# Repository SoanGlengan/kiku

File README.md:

# kiku
<h2>meshtastic device but open source</h2>
<p>small meshtastic device that is using a esp32 and sx1262</p>

<a href="https://docs.google.com/spreadsheets/d/1daOj9rbJtqAOdZNNDehtXnfdnzQVLjkryvcnbeCaL2A/edit?usp=sharing"><b>The Bill of Materials<b/><a/>

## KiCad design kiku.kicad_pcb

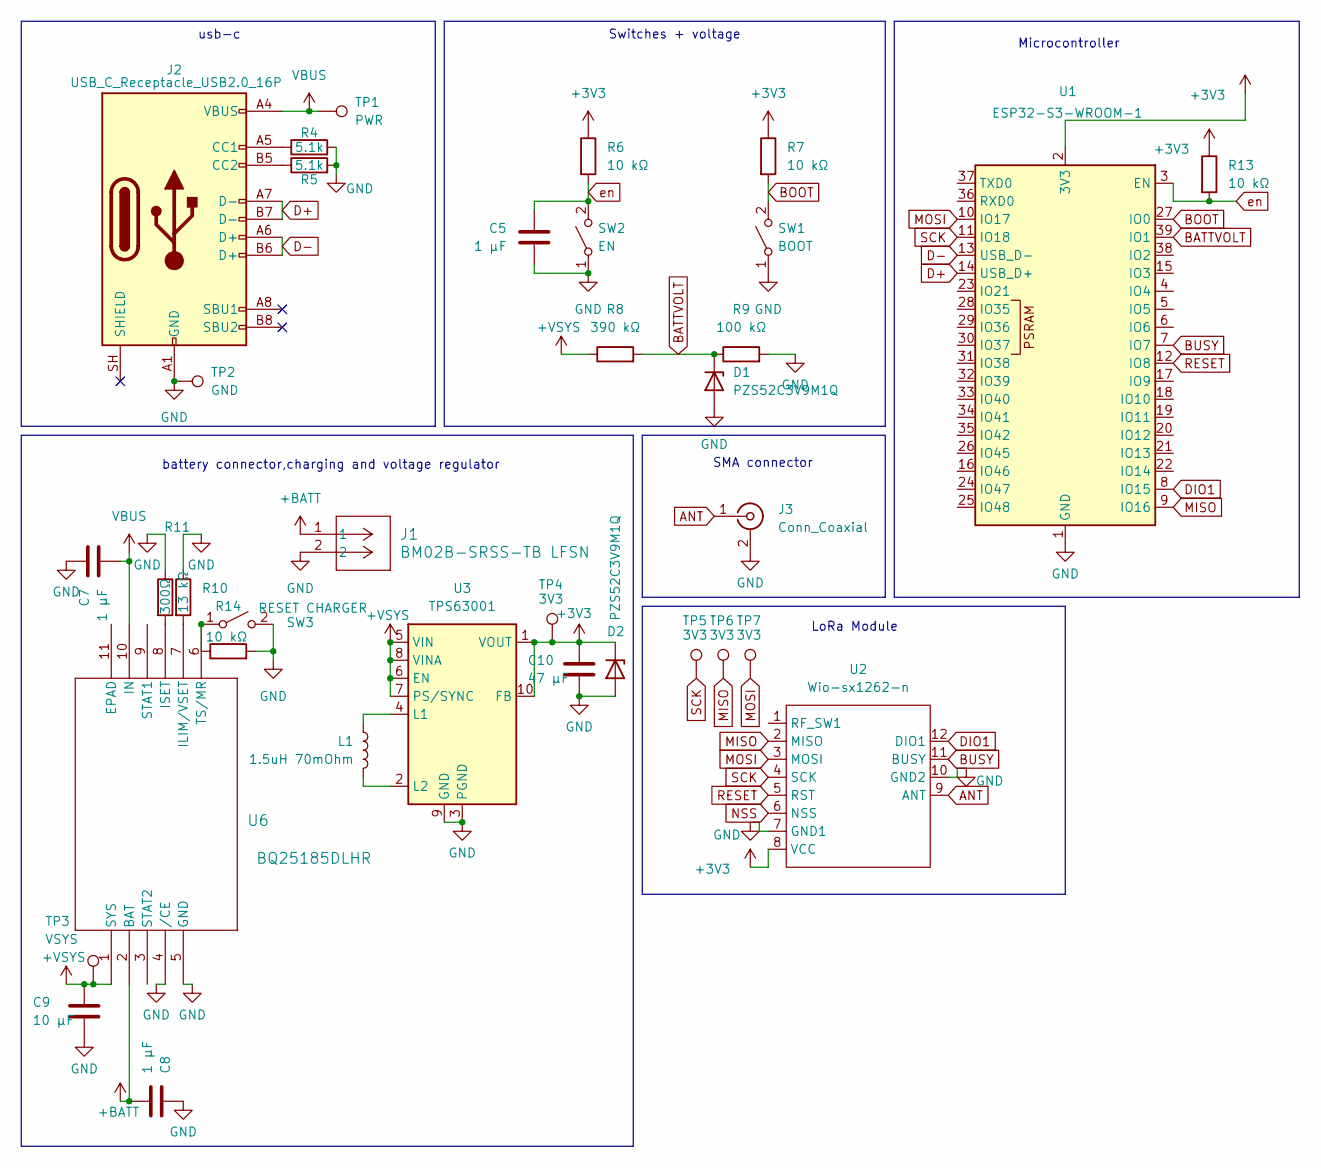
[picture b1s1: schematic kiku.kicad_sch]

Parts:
C5, C7, C8: 1 µF; C_0603_1608Metric
C9: 10 µF; C_0603_1608Metric
C10: 47 µF; C_0603_1608Metric
D1, D2: PZS52C3V9M1Q; D_0402_1005Metric
J1: BM02B-SRSS-TB LFSN; CONN_BM02B-SRSS-TB_JST
J2: USB_C_Receptacle_USB2.0_16P; USB_C_Receptacle_GCT_USB4105-xx-A_16P_TopMnt_Horizontal
J3: Conn_Coaxial; SMA_Molex_73251-1153_EdgeMount_Horizontal
L1: 1.5uH 70mOhm; L_1008_2520Metric
R4, R5: 5.1k; R_0402_1005Metric
R6, R7, R13, R14: 10 kΩ; R_0402_1005Metric
R8: 390 kΩ; R_0402_1005Metric
R9: 100 kΩ; R_0402_1005Metric
R10: 13 kΩ; R_0402_1005Metric
R11: 300Ω; R_0402_1005Metric
SW1: BOOT; SW_SPST_B3U-1100P
SW2: EN; SW_SPST_B3U-1100P
SW3: RESET CHARGER; SW_SPST_B3U-1100P
TP1: PWR; smalltestpoint
TP2: GND; smalltestpoint
TP3: VSYS; smalltestpoint
TP4, TP5, TP6, TP7: 3V3; smalltestpoint
U1: ESP32-S3-WROOM-1
U2: Wio-sx1262-n; Wio-SX1262 PCB Package
U3: TPS63001; Texas_DRC0010J_ThermalVias
U6: BQ25185DLHR; WSON10_DLH_TEX

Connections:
+3V3: C10.1, D2.1 (K), R6.1, R7.1, R13.1, TP4.1 (1_1), U1.2 (3V3), U2.8 (VCC), U3.1 (VOUT), U3.10 (FB)
+BATT: C8.2, J1.1, U6.2 (BAT)
+VSYS: C9.1, R8.1, TP3.1 (1_1), U3.5 (VIN), U3.6 (EN), U3.7 (PS/SYNC), U3.8 (VINA), U6.1 (SYS)
ANT: J3.1 (In), U2.9 (ANT)
BATTVOLT: D1.1 (K), R8.2, R9.1, U1.39 (IO1)
BOOT: R7.2, SW1.2 (B), U1.27 (IO0)
BUSY: U1.7 (IO7), U2.11 (BUSY)
D+: J2.A7 (D-), J2.B7 (D-), U1.14 (USB_D+)
D-: J2.A6 (D+), J2.B6 (D+), U1.13 (USB_D-)
DIO1: U1.8 (IO15), U2.12 (DIO1)
GND: C5.2, C7.1, C8.1, C9.2, C10.2, D1.2 (A), D2.2 (A), J1.2, J2.A1 (GND), J2.A12 (GND), J2.B1 (GND), J2.B12 (GND), J3.2 (Ext), R4.2, R5.2, R9.2, R10.1, R11.1, R14.2, SW1.1 (A), SW2.1 (A), SW3.2 (B), TP2.1 (1_1), U1.1 (GND), U1.40 (GND), U1.41 (GND), U2.7 (GND1), U2.10 (GND2), U3.3 (PGND), U3.9 (GND), U3.11 (PGND), U6.4 (/CE), U6.5 (GND)
MISO: TP6.1 (1_1), U1.9 (IO16), U2.2 (MISO)
MOSI: TP7.1 (1_1), U1.10 (IO17), U2.3 (MOSI)
NSS: U2.6 (NSS)
unnamed: J2.A5 (CC1), R4.1
unnamed: J2.B5 (CC2), R5.1
unnamed: R14.1, SW3.1 (A), U6.6 (TS/MR)
unnamed: L1.2, U3.4 (L1)
unnamed: L1.1, U3.2 (L2)
unnamed: R10.2, U6.7 (ILIM/VSET)
unnamed: R11.2, U6.8 (ISET)
RESET: U1.12 (IO8), U2.5 (RST)
SCK: TP5.1 (1_1), U1.11 (IO18), U2.4 (SCK)
VBUS: C7.2, J2.A4 (VBUS), J2.A9 (VBUS), J2.B4 (VBUS), J2.B9 (VBUS), TP1.1 (1_1), U6.10 (IN)
en: C5.1, R6.2, R13.2, SW2.2 (B), U1.3 (EN)

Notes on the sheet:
battery connector,charging and voltage regulator
LoRa Module
usb-c
Microcontroller
Switches + voltage
SMA connector

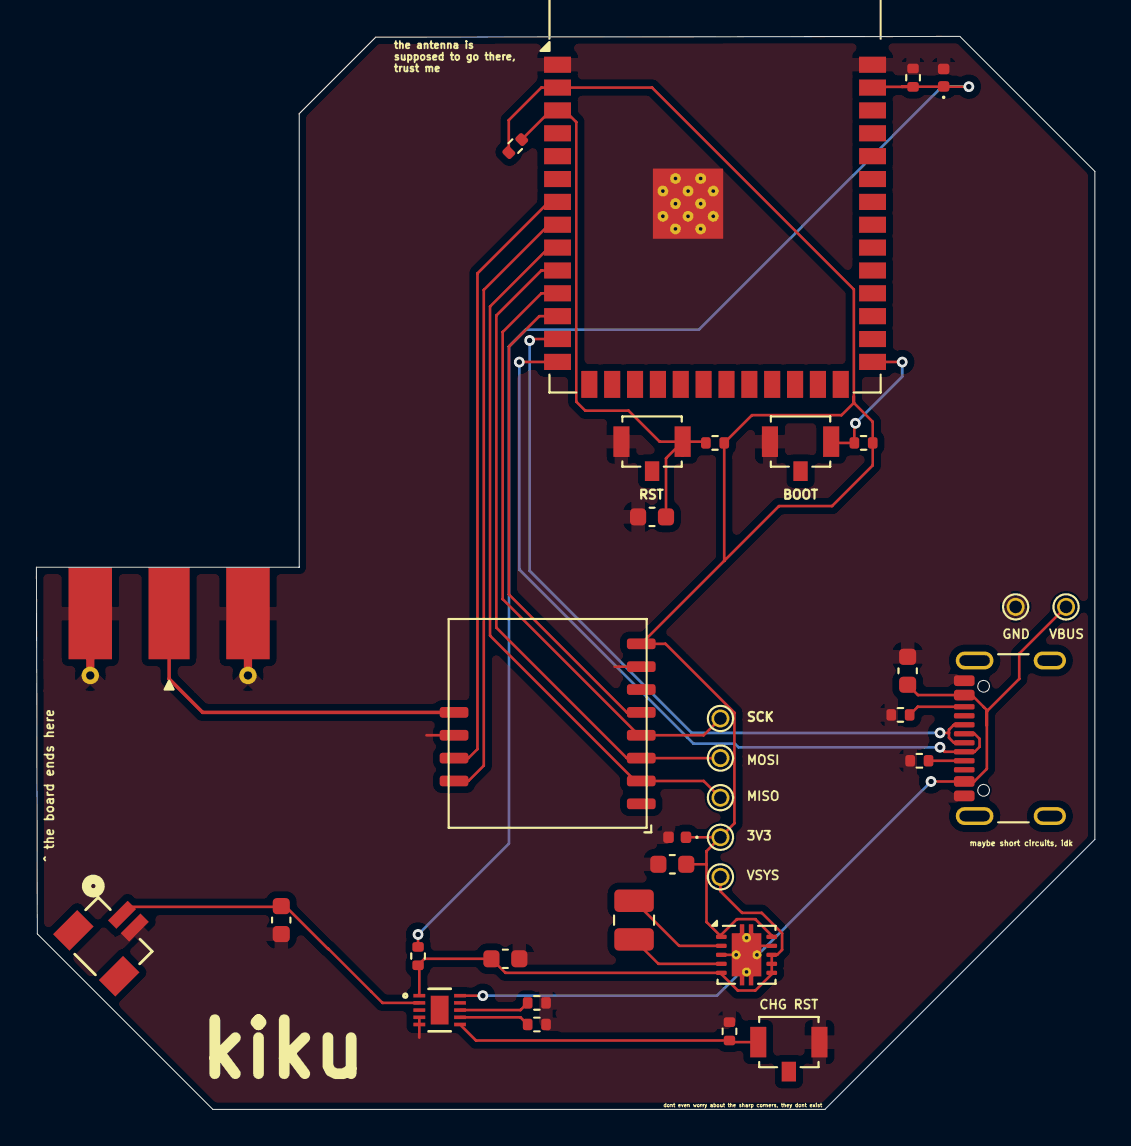
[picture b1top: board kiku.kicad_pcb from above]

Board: 2 copper layers, 58.8 x 59.6 mm, 35 parts (0 on the bottom side), 24 nets.

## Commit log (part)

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2026-05-27 add the files
2026-05-27 test
2026-05-29 add the microcontroller and stuff
2026-06-04 a lot of connections are done
2026-06-08 quite a bit of changes, still not finished with the schematic. havent committed in a while
2026-06-10 more work on the power stuff
2026-06-12 mostly finished on the schematic, possibly starting on the routing
2026-06-13 think im mostly finished
2026-06-14 wow i have a lot to do
2026-06-27 second attempt of routing
